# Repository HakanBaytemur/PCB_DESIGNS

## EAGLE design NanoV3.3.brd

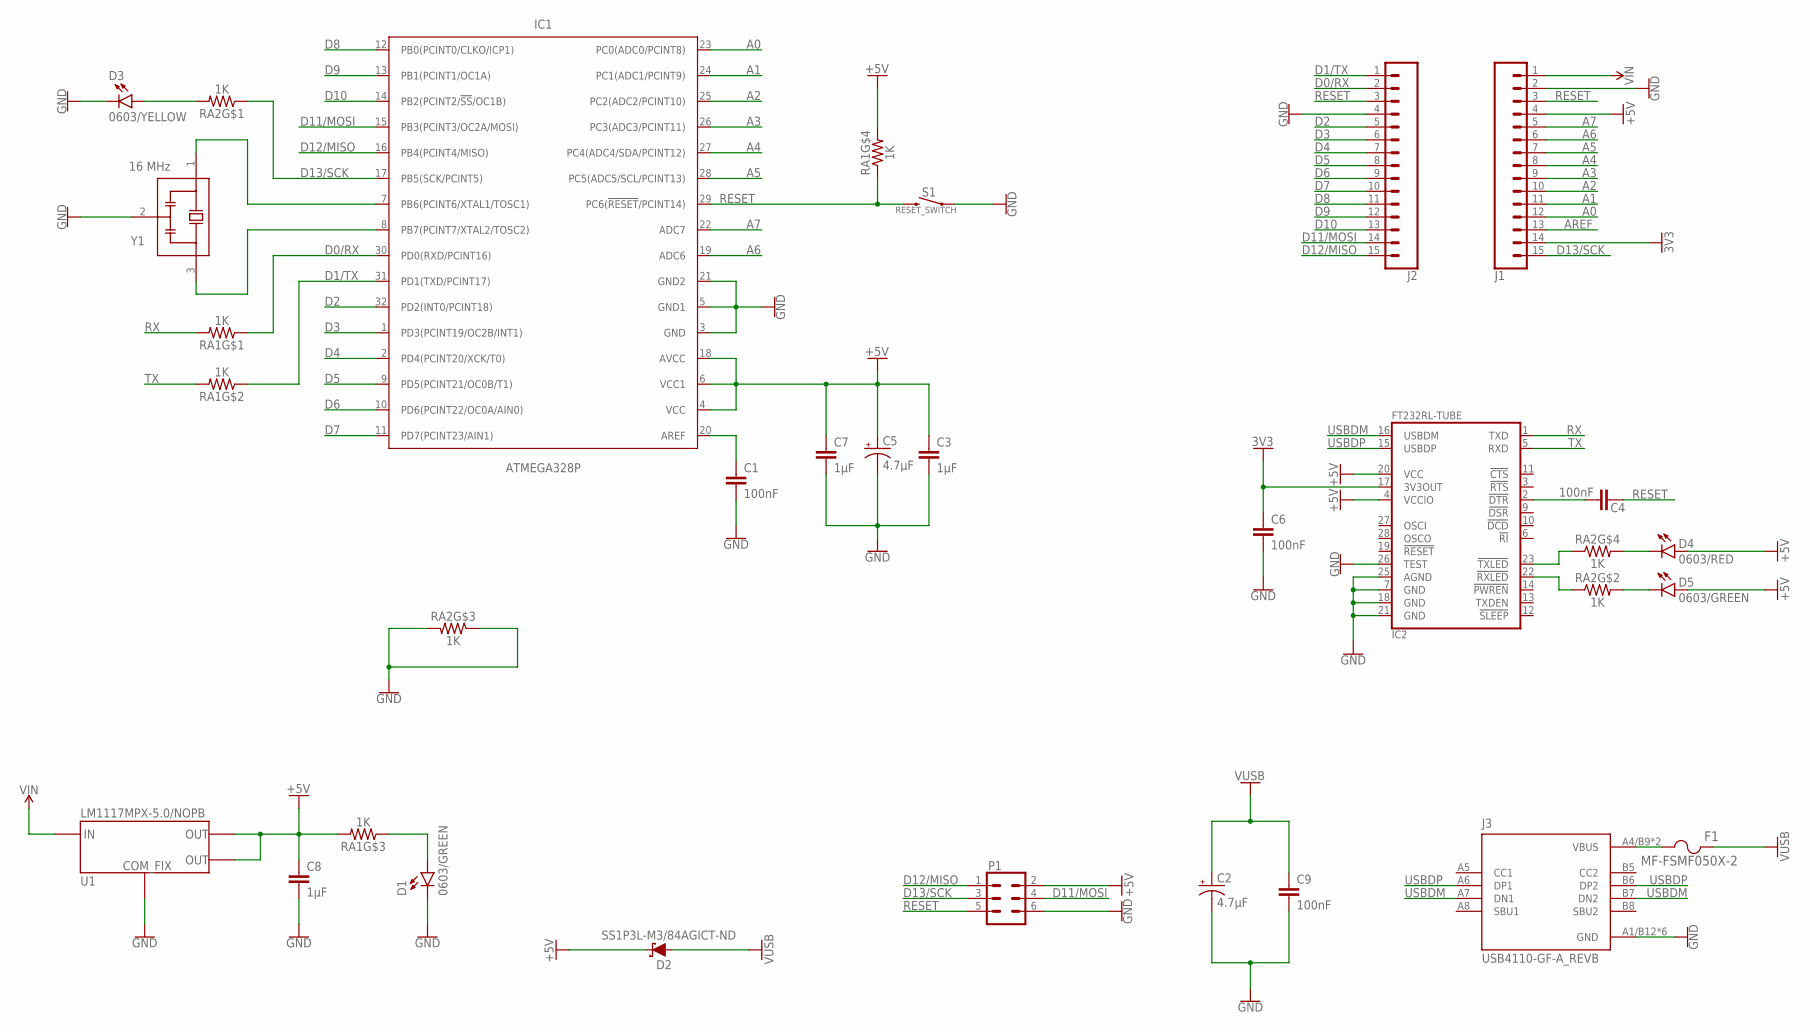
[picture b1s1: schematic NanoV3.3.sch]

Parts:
C1, C4, C6, C9: 100nF; CAP_0603(1608_METRIC)
C2, C5: 4.7μF; CAP_TANT_1206(3216_METRIC)_TYPE_A_MAX
C3, C7, C8: 1μF; CAP_0603(1608_METRIC)
D1, D5: 0603/GREEN; LED_0603(1608_METRIC)_GREEN
D2: SS1P3L-M3/84AGICT-ND; DO-220AA(SMP)-M
D3: 0603/YELLOW; LED_0603(1608_METRIC)_YELLOW
D4: 0603/RED; LED_0603(1608_METRIC)_RED
F1: MF-FSMF050X-2; PTC_FUSE_0603(1608_METRIC)
IC1: ATMEGA328P; 32-TQFP
IC2: FT232RL-TUBE; 28-SSOP
J1, J2: CONN_15_M_180C; HDRV15W64P254_1X15_3810X254X838B
J3: USB4110-GF-A_REVB; GCT_USB4110-GF-A_REVB
P1: CONN_2X3_M_180C; HDRV6W64P254_2X3_762X508X838B
RA1, RA2: 1K; RESISTOR_ARRAY_1206(3216_METRIC)_WIDE
S1: RESET SWITCH; SW_TS09-63-25-WT-260-SMT-TR
U1: LM1117MPX-5.0/NOPB; SOT-223-4
Y1: 16 MHz; RESONATOR_SMD-3(3.20MMX1.30MM)

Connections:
3V3: C6.1, IC2.17 (3V3OUT), J1.14
+5V: C3.1, C5.1 (+), C7.1, C8.1, D2.1 (C), D4.A, D5.A, IC1.4 (VCC), IC1.6 (VCC1), IC1.18 (AVCC), IC2.4 (VCCIO), IC2.20 (VCC), J1.4, P1.2, RA1.5 (2), RA1.6 (2), U1.2 (OUTPUT_JUNCTİON), U1.4 (OUTPUT_TAB)
A0: IC1.23 (PC0(ADC0/PCINT8)), J1.12
A1: IC1.24 (PC1(ADC1/PCINT9)), J1.11
A2: IC1.25 (PC2(ADC2/PCINT10)), J1.10
A3: IC1.26 (PC3(ADC3/PCINT11)), J1.9
A4: IC1.27 (PC4(ADC4/SDA/PCINT12)), J1.8
A5: IC1.28 (PC5(ADC5/SCL/PCINT13)), J1.7
A6: IC1.19 (ADC6), J1.6
A7: IC1.22 (ADC7), J1.5
AREF: C1.1, IC1.20 (AREF), J1.13
D0/RX: IC1.30 (PD0(RXD/PCINT16)), J2.2, RA1.1
D1/TX: IC1.31 (PD1(TXD/PCINT17)), J2.1, RA1.2 (1)
D2: IC1.32 (PD2(INT0/PCINT18)), J2.5
D3: IC1.1 (PD3(PCINT19/OC2B/INT1)), J2.6
D4: IC1.2 (PD4(PCINT20/XCK/T0)), J2.7
D5: IC1.9 (PD5(PCINT21/OC0B/T1)), J2.8
D6: IC1.10 (PD6(PCINT22/OC0A/AIN0)), J2.9
D7: IC1.11 (PD7(PCINT23/AIN1)), J2.10
D8: IC1.12 (PB0(PCINT0/CLKO/ICP1)), J2.11
D9: IC1.13 (PB1(PCINT1/OC1A)), J2.12
D10: IC1.14 (PB2(PCINT2/!SS!/OC1B)), J2.13
D11/MOSI: IC1.15 (PB3(PCINT3/OC2A/MOSI)), J2.14, P1.4
D12/MISO: IC1.16 (PB4(PCINT4/MISO)), J2.15, P1.1
D13/SCK: IC1.17 (PB5(SCK/PCINT5)), J1.15, P1.3, RA2.1
DTR: C4.2, IC2.2 (!DTR)
GND: C1.2, C2.2 (-), C3.2, C5.2 (-), C6.2, C7.2, C8.2, C9.2, D1.C, D3.C, IC1.3 (GND), IC1.5 (GND1), IC1.21 (GND2), IC2.7 (GND), IC2.18 (GND), IC2.21 (GND), IC2.25 (AGND), IC2.26 (TEST), J1.2, J2.4, J3.A1/B12 (GND), J3.B1/A12 (GND), J3.S1 (GND), J3.S2 (GND), J3.S3 (GND), J3.S4 (GND), P1.6, RA2.3 (1), RA2.6 (2), S1.1, U1.1 (COMMON_FIXED), Y1.2 (GND)
unnamed: D3.A, RA2.8 (2)
unnamed: D1.A, RA1.3 (1)
unnamed: F1.1, J3.A4/B9 (VBUS), J3.B4/A9 (VBUS)
unnamed: D4.C, RA2.5 (2)
unnamed: D5.C, RA2.7 (2)
OSC1: IC1.7 (PB6(PCINT6/XTAL1/TOSC1)), Y1.1 (IN)
OSC2: IC1.8 (PB7(PCINT7/XTAL2/TOSC2)), Y1.3 (OUT)
RESET: C4.1, IC1.29 (PC6(!RESET!/PCINT14)), J1.3, J2.3, P1.5, RA1.4 (1), S1.2
RX: IC2.1 (TXD), RA1.8 (2)
RXLED: IC2.22 (!RXLED), RA2.2 (1)
TX: IC2.5 (RXD), RA1.7 (2)
TXLED: IC2.23 (!TXLED), RA2.4 (1)
USBDM: IC2.16 (USBDM), J3.A7 (DN1), J3.B7 (DN2)
USBDP: IC2.15 (USBDP), J3.A6 (DP1), J3.B6 (DP2)
VIN: J1.1, U1.3 (INPUT)
VUSB: C2.1 (+), C9.1, D2.2 (A), F1.2

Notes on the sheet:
RESET_SWITCH

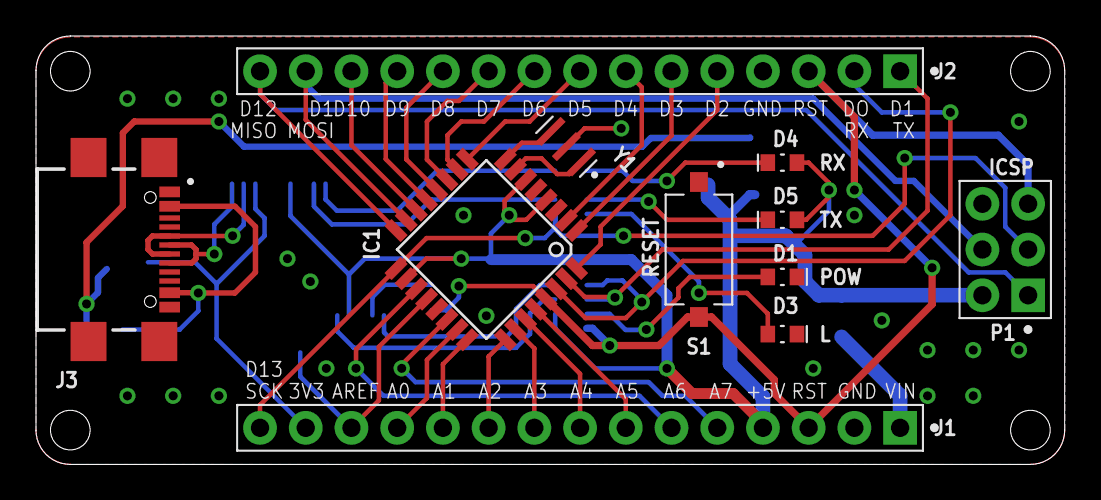
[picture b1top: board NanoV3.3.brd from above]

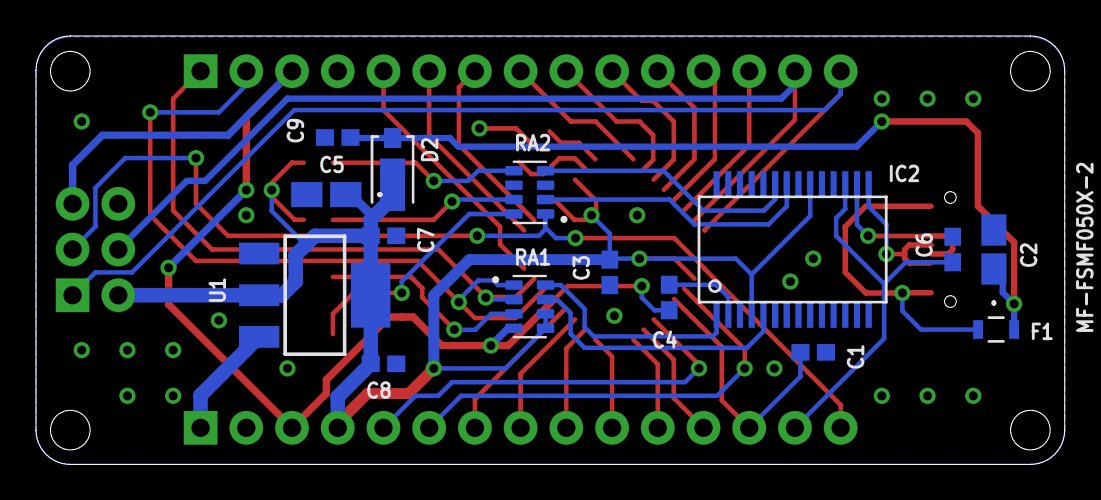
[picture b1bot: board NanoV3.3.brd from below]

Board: 2 copper layers, 57.1 x 23.8 mm, 26 parts (15 on the bottom side), 43 nets.

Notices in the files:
parts and their libraries:
COPYRIGHT: Copyright (C) 2022 Ultra Librarian. All rights reserved.
SparkFun-PowerSymbols: Licensing: Creative Commons ShareAlike 4.0 International - https://creativecommons.org/licenses/by-sa/4.0
